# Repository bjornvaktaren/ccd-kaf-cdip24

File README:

To-do
-----

- Check that you can control the servo with 3.3V.
- Change to HX1K with VQ-100 package? Does the logic fit?

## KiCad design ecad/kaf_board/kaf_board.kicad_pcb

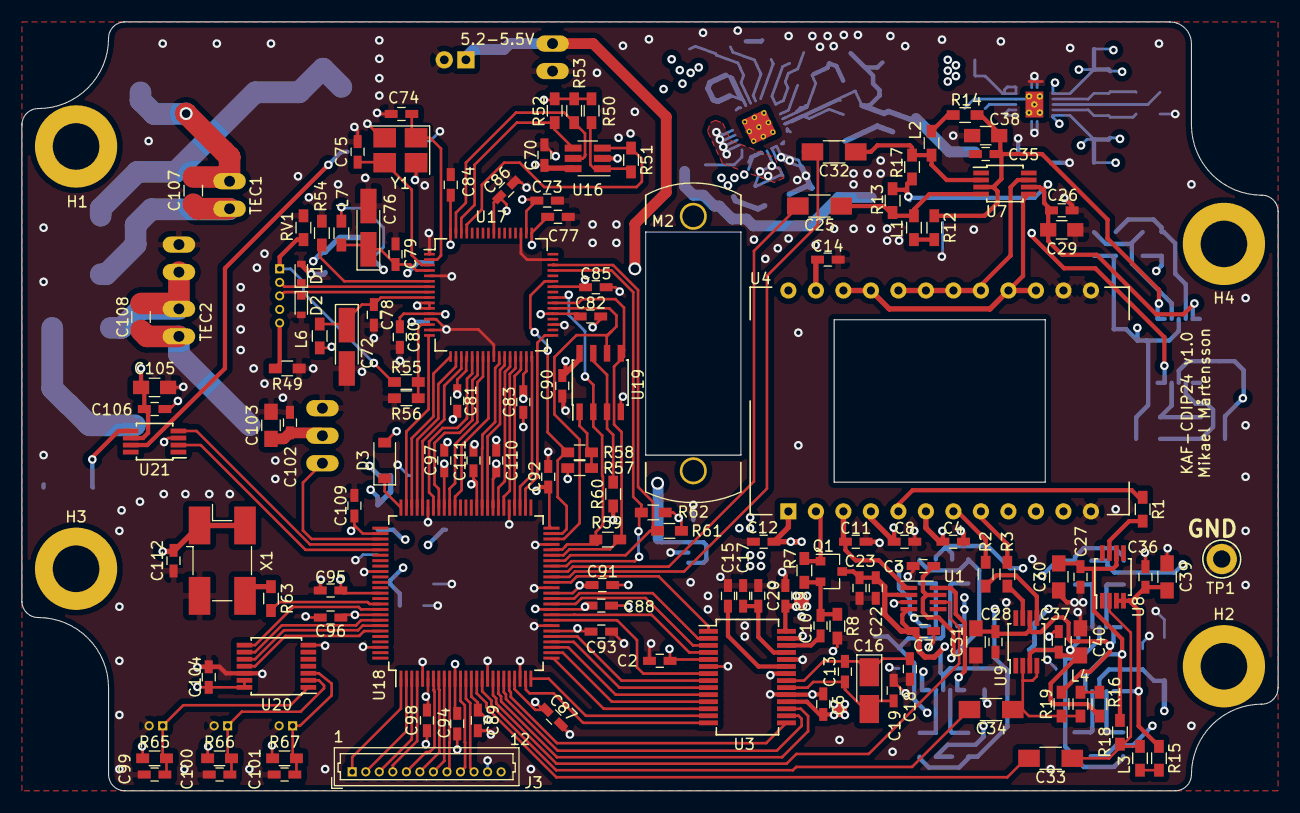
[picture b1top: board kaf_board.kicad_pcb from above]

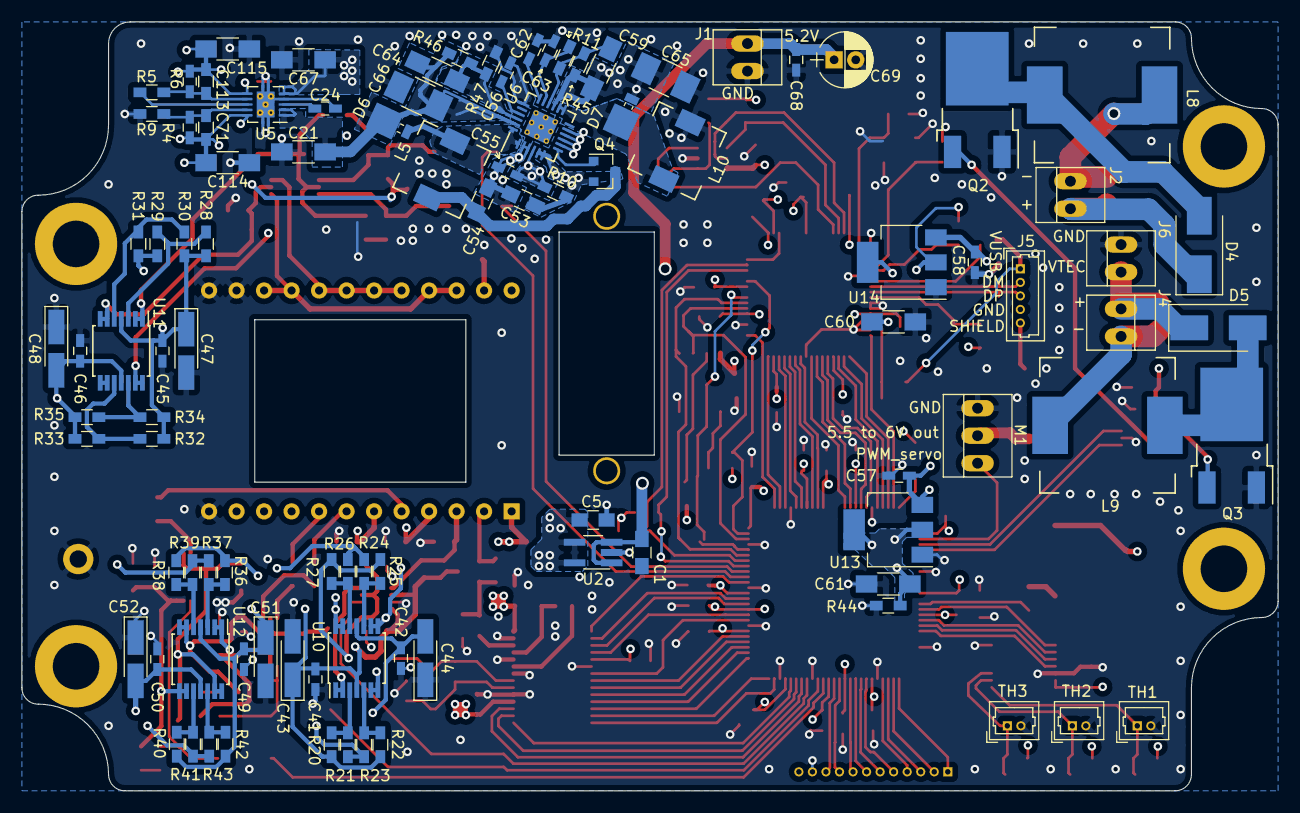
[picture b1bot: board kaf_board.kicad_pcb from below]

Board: 4 copper layers, 116.0 x 71.0 mm, 240 parts (99 on the bottom side), 159 nets.

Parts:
C1, C5: 2.2u X7R; C_0805_HandSoldering
C2, C3, C6, C7, C9, C10, C13, C15, C17, C18, C19, C23, C24, C26, C27, C28, C35, C36, C37, C41, C42, C45, C46, C49, C50, C55, C57, C58, C68, C70, C73, C78, C79, C80, C81, C82, C83, C84, C85, C86, C87, C88, C89, C90, C91, C92, C93, C94, C95, C96, C97, C98, C99, C100, C101, C102, C106, C109, C110, C111, C112: 0.1u; C_0603_HandSoldering
C4, C8, C11, C12, C14: 0; C_0603_HandSoldering
C16: 10u; CP_Tantalum_Case-R_EIA-2012-12_Hand
C20, C22, C104: 1u; C_0603_HandSoldering
C21, C60, C61, C67, C114, C115: 10u; C_1206_HandSoldering
C25, C32, C33, C34: 33u; C_1206_HandSoldering
C29, C30, C31, C38, C39, C40, C53, C54, C103, C105, C107, C108: 4.7u; C_0805_HandSoldering
C43, C44, C47, C48, C51, C52: 4.7u; CP_Tantalum_Case-A_EIA-3216-18_Hand
C56, C71, C113: 10n; C_0603_HandSoldering
C59: populate? No. (5.6p); C_1206_HandSoldering
C62: 4.7n; C_0603_HandSoldering
C63: 220n; C_0603_HandSoldering
C64: 6.8p; C_1206_HandSoldering
C65, C66: 22u; C_1210_HandSoldering
C69: 47u; CP_Radial_D5.0mm_P2.00mm
C72, C76: 4.7u tan; CP_Tantalum_Case-A_EIA-3216-18_Hand
C74, C75: 27p; C_0603_HandSoldering
C77: 3.3u; C_0603_HandSoldering
D1, D2: PGB101; D_0603
D3: 1N5819; D_SOD-123
D4, D5: VS-4EGU06-M3; D_SMB_Handsoldering
D6, D7: MBRM120; D_Powermite_AK
H1, H2, H3, H4: MountingHole; MountingHole_4.3mm_M4_ISO7380_Pad
J1: PWR; PINHEAD1-2
J2: TEC1; PINHEAD1-2
J3: Conn_01x12; Molex_PicoBlade_53047-1210_12x1.25mm_Straight
J4: TEC2; PINHEAD1-2
J5: USB; Molex_PicoBlade_53047-0510_05x1.25mm_Straight
J6: TECPWR; PINHEAD1-2
L1, L2, L3, L4: 1u; L_0603_HandSoldering
L5, L10: 4.7u; L_SMT_B82462G4
L6, L7: 600R/0.5A; L_0603_HandSoldering
L8, L9: 100u; L_Bourns_1210
M1: Motor_Servo; PINHEAD1-3
M2: Servo cut-out; HD-1440A
Q1: MMBT3904LT1G; SOT-23
Q2, Q3: NTD4804N; ONSemi_DPAK-3_5.97x6.35mm
Q4: Si2323DS; SOT-23
R1, R2, R3: 68; R_0603_HandSoldering
R4: 169k 0.1%; R_0603_HandSoldering
R5: 12k 0.1%; R_0603_HandSoldering
R6: 147k 0.1%; R_0603_HandSoldering
R7: 140; R_0603_HandSoldering
R8, R12, R14, R15, R16: 1k; R_0603_HandSoldering
R9: 15k 0.1%; R_0603_HandSoldering
R10: 100; R_0603_HandSoldering
R11: 104.8k; R_0603_HandSoldering
R13, R17, R18, R19, R49: NA; R_0603_HandSoldering
R20, R21, R22, R23, R24, R25, R26, R27, R28, R29, R30, R31, R32, R33, R34, R35, R36, R37, R38, R39, R40, R41, R42, R43: R; R_0603_HandSoldering
R44: 120; R_0603_HandSoldering
R45: 1.3M; R_0603_HandSoldering
R46: 975k; R_0603_HandSoldering
R47: 85.8k; R_0603_HandSoldering
R50, R52, R53, R56, R57, R60, R61, R65, R66, R67: 10k; R_0603_HandSoldering
R51: 2k; R_0603_HandSoldering
R54: 12k 1%; R_0603_HandSoldering
R55: 4.7k; R_0603_HandSoldering
R58, R63: 22; R_0603_HandSoldering
R59: NA(22); R_0603_HandSoldering
R62: 2.2k; R_0603_HandSoldering
RV1: V5.5MLA; R_0603_HandSoldering
TH1, TH2, TH3: 2000, beta 3500; Molex_PicoBlade_53047-0210_02x1.25mm_Straight
TP1: GND; Test_Point_Keystone_5005-5009_Compact
U1: MAX4649; SOT-23-8_Handsoldering
U2: ADP7118AUJZ; TSOT-23-5_HandSoldering
U3: AD9826; SSOP-28_5.3x10.2mm_Pitch0.65mm
U4: KAF-CDIP24; CDIP-24_20.2x34.5mm_P2.54mm
U5: TPS7A39; TI_WSON-10-1TP_3x3mm_P0.5mm_HandSolder
U6: TPS6513x; TI_WQFN-24-1EP_4x4mm_P0.5mm_HandSolder
U7, U8, U21: TC4427; MSOP-8_3x3mm_Pitch0.65mm
U9: TC4428; MSOP-8_3x3mm_Pitch0.65mm
U10, U11, U12: LM224; TSSOP-14_4.4x5mm_Pitch0.65mm
U13: LD1117S12CTR_SOT223; SOT-223-3_TabPin2
U14: LD1117S33CTR_SOT223; SOT-223-3_TabPin2
U16: 93LCxxBxxOT; SOT-23-6_Handsoldering
U17: FT2232HL; LQFP-64_10x10mm_Pitch0.5mm
U18: ICE40HX1K-VQ100; LQFP-100_14x14mm_Pitch0.5mm
U19: W25X20CL; SOIC-8_3.9x4.9mm_Pitch1.27mm
U20: MCP3004; TSSOP-14_4.4x5mm_Pitch0.65mm
X1: KC7050A-C3; Oscillator_SMD_EuroQuartz_XO91-4pin_7.0x5.0mm_HandSoldering
Y1: 12 MHz; Crystal_SMD_3225-4pin_3.2x2.5mm_HandSoldering

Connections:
+1V2: C61.1, C88.1, C94.1, C109.1, C111.1, R44.2, U13.2, U18.11, U18.35, U18.61, U18.77
+3V3: C2.2, C60.1, C70.1, C73.1, C81.1, C83.1, C85.1, C86.1, C87.1, C89.1, C90.1, C91.1, C92.1, C93.1, C95.1, C96.1, C97.1, C98.1, C104.1, C110.1, C112.1, D3.2, J3.12, L6.2, L7.2, R50.1, R52.1, R53.1, R57.2, R60.1, R61.1, R62.1, R65.1, R66.1, R67.1, U3.5, U14.2, U16.6, U17.20, U17.31, U17.42, U17.50, U17.56, U18.6, U18.14, U18.22, U18.31, U18.38, U18.50, U18.58, U18.67, U18.88, U18.92, U19.8, U20.13, U20.14, X1.1, X1.4
+6V: C1.2, C53.1, C57.1, C58.1, C68.1, C69.1, C102.1, C103.1, J1.1, M1.2, Q4.2, R10.2, U2.1, U2.3, U6.5, U6.6, U13.3, U14.3
+14.5V: C7.2, C22.2, C23.2, C41.2, C43.1, C45.2, C47.1, C49.2, C51.1, C71.2, C114.2, Q1.3, R4.1, R20.1, R22.1, R24.1, R26.1, R28.1, R30.1, R32.1, R34.1, R36.1, R38.1, R40.1, R42.1, U1.2, U1.4, U5.10, U10.4, U11.4, U12.4
-14.5V: C3.2, C42.2, C44.2, C46.2, C48.2, C50.2, C52.2, C113.1, C115.2, R6.2, R21.2, R23.2, R25.2, R27.2, R29.2, R31.2, R33.2, R35.2, R37.2, R39.2, R41.2, R43.2, U1.7, U5.6, U10.11, U11.11, U12.11
/ccd/AD_ADCLK: U3.3, U18.36
/ccd/AD_CDSCLK1: U3.1, U18.40
/ccd/AD_CDSCLK2: U3.2, U18.37
/ccd/AD_D0: U3.14, U18.24
/ccd/AD_D1: U3.13, U18.25
/ccd/AD_D2: U3.12, U18.26
/ccd/AD_D3: U3.11, U18.27
/ccd/AD_D4: U3.10, U18.28
/ccd/AD_D5: U3.9, U18.29
/ccd/AD_D6: U3.8, U18.30
/ccd/AD_D7: U3.7, U18.33
/ccd/AD_OEB: U3.4, U18.34
/ccd/AD_SCLK: U3.16, U18.20
/ccd/AD_SDATA: U3.15, U18.21
/ccd/AD_SLOAD: U3.17, U18.19
/ccd/AMP_OFF: U1.6, U18.18
/ccd/AVDD: C5.2, C6.2, C9.2, U2.4, U2.5, U3.18, U3.28
/ccd/H1: R2.2, U9.5
/ccd/H2: R3.2, U9.7
/ccd/H_3.3V: C34.2, U18.16
/ccd/R: R1.2, U8.7
/ccd/R_3.3V: C33.2, U18.15
/ccd/V1: U4.15, U4.16, U4.21, U4.22, U7.5
/ccd/V1_3.3V: C25.2, U18.42
/ccd/V2: U4.17, U4.18, U4.19, U4.20, U7.7
/ccd/VGUARD: C14.1, U4.23, U11.13, U11.14
/ccd/VOG: C12.1, U4.1, U10.6, U10.7
/ccd/VOUT_BUF: C10.1, Q1.2, R7.1, R8.1
/ccd/VRD: C8.1, U4.4, U10.8, U10.9
/ccd/VSS: C4.1, U4.6, U10.13, U10.14
/ccd/V_AMP: C11.1, U1.1, U4.3
/ccd/V_AMPL: U1.8, U10.1, U10.2
/ccd/V_HH: C28.2, C31.2, R19.1, U9.6, U12.6, U12.7
/ccd/V_HL: C37.2, C40.2, R16.1, U9.3, U12.1, U12.2
/ccd/V_RH: C27.2, C30.2, R18.1, U8.6, U12.13, U12.14
/ccd/V_RL: C36.2, C39.2, R15.1, U8.3, U8.4, U12.8, U12.9
/ccd/V_VH: C26.2, C29.2, R13.1, R17.1, U7.6, U11.6, U11.7
/ccd/V_VL: C35.2, C38.2, R12.1, R14.1, U7.3, U11.1, U11.2
/ccd/ccd_voltage_2/V3: U11.8, U11.9
/fpga/AUX1: J3.1, U18.1
/fpga/AUX2: J3.2, U18.2
/fpga/AUX3: J3.3, U18.3
/fpga/AUX4: J3.4, U18.4
/fpga/AUX5: J3.5, U18.7
/fpga/AUX6: J3.6, U18.8
/fpga/AUX7: J3.7, U18.9
/fpga/AUX8: J3.8, U18.10
/fpga/AUX9: J3.9, U18.12
/fpga/AUX10: J3.10, U18.13
/fpga/CLK: R63.1, U18.90
/fpga/FT_CLKOUT: U17.32, U18.53
/fpga/FT_D0: U17.16, U18.74
/fpga/FT_D1: U17.17, U18.73
/fpga/FT_D2: U17.18, U18.72
/fpga/FT_D3: U17.19, U18.71
/fpga/FT_D4: U17.21, U18.69
/fpga/FT_D5: U17.22, U18.68
/fpga/FT_D6: U17.23, U18.66
/fpga/FT_D7: U17.24, U18.65
/fpga/FT_OE#: U17.33, U18.52
/fpga/FT_RD#: U17.28, U18.57
/fpga/FT_RXF#: U17.26, U18.60
/fpga/FT_SIWUA: U17.30, U18.54
/fpga/FT_TXE#: U17.27, U18.59
/fpga/FT_WR#: U17.29, U18.56
/fpga/MCP_CLK: U18.95, U20.11
/fpga/MCP_CS_N: U18.91, U20.8
/fpga/MCP_DIN: U18.93, U20.9
/fpga/MCP_DOUT: U18.94, U20.10
/fpga/PWM_SERVO: M1.1, U18.78
/fpga/PWM_TEC1: U18.80, U21.2
/fpga/PWM_TEC2: U18.79, U21.4
/fpga/V1_3.3V: C32.2, U18.41
/fpga/VPP_2V5: D3.1, U18.75
/power/+15V: C21.2, C64.1, C66.1, D6.1, R46.2, U5.1, U5.2, U6.23
/power/-15V: C59.2, C65.1, C67.2, D7.2, R45.1, U5.5, U6.15
/thermo_and_mechanical/V_TEC: C105.1, C106.1, C107.1, C108.1, D4.1, D5.1, J2.1, J4.1, J6.1, U21.6
/usb-interface/DM: D1.1, J5.2, U17.7
/usb-interface/DP: D2.1, J5.3, U17.8
/usb-interface/FT_CDONE: R62.2, U17.45, U18.43
/usb-interface/FT_CRESET: R61.2, U17.46, U18.44
/usb-interface/FT_MISO: R59.1, U17.40, U18.46, U19.2
/usb-interface/FT_MOSI: R59.2, U17.39, U18.45, U19.5
/usb-interface/FT_SCK: U17.38, U18.48, U19.6
/usb-interface/FT_SS: R58.1, U17.43, U18.49
/usb-interface/VPHY: C76.1, C79.1, L7.1, U17.4
/usb-interface/VREG: C77.1, C80.1, C82.1, C84.1, U17.12, U17.37, U17.49, U17.64
/usb-interface/VUSB: J5.1, R55.2, RV1.2
GND: C1.1, C2.1, C3.1, C4.2, C5.1, C6.1, C7.1, C8.2, C9.1, C11.2, C12.2, C14.2, C15.2, C17.1, C18.2, C19.2, C20.1, C21.1, C22.1, C23.1, C24.1, C26.1, C27.1, C28.1, C29.1, C30.1, C31.1, C35.1, C36.1, C37.1, C38.1, C39.1, C40.1, C41.1, C42.1, C43.2, C44.1, C45.1, C46.1, C47.2, C48.1, C49.1, C50.1, C51.2, C52.1, C53.2, C54.2, C55.2, C56.2, C57.2, C58.2, C60.2, C61.2, C62.2, C63.2, C65.2, C66.2, C67.1, C68.2, C69.2, C70.2, C72.2, C73.2, C74.2, C75.1, C76.2, C77.2, C78.2, C79.2, C80.2, C81.2, C82.2, C83.2, C84.2, C85.2, C86.2, C87.2, C88.2, C89.2, C90.2, C91.2, C92.2, C93.2, C94.2, C95.2, C96.2, C97.2, C98.2, C99.2, C100.2, C101.2, C102.2, C103.2, C104.2, C105.2, C106.2, C109.2, C110.2, C111.2, C112.2, C114.1, C115.1, D1.2, D2.2, J1.2, J3.11, J5.4, J6.2, L10.1, M1.3, Q2.3, Q3.3, R8.2, R9.2, R44.1, R47.1, R49.1, R54.1, R56.2, RV1.1, TH1.2, TH2.2, TH3.2, TP1.1, U1.3, U2.2, U3.6, U3.19, U3.22, U3.24, U3.27, U4.12, U4.13, U4.14, U5.4, U5.11, U6.2, U6.3, U6.19, U6.25, U13.1, U14.1, U16.2, U17.1, U17.5, U17.10, U17.11, U17.13, U17.15, U17.25, U17.35, U17.47, U17.51, U18.5, U18.17, U18.23, U18.32, U18.39, U18.47, U18.55, U18.70, U18.84, U18.98, U19.4, U20.7, U20.12, U21.3, X1.2, Y1.2, Y1.4
GNDPWR: J5.5, R49.2
unnamed: C10.2, U3.26
unnamed: C13.1, C16.2, C19.1, U3.20
unnamed: C13.2, C16.1, C18.1, U3.21
unnamed: C15.1, U3.23
unnamed: C17.2, C20.2, U3.25
unnamed: C24.2, U5.3
unnamed: C25.1, L1.2, R13.2, U7.4
unnamed: C32.1, L2.2, R17.2, U7.2
unnamed: C33.1, L3.2, R18.2, U8.2
unnamed: C34.1, L4.2, R19.2, U9.2, U9.4
unnamed: C54.1, L5.2, Q4.3
unnamed: C55.1, R10.1, U6.4, U6.8, U6.9, U6.10, U6.11
unnamed: C56.1, U6.21
unnamed: C59.1, R11.1, R45.2, U6.16
unnamed: C62.1, U6.18
unnamed: C63.1, R11.2, U6.17
unnamed: C64.2, R46.1, R47.2, U6.22
unnamed: C71.1, R4.2, R9.1, U5.9
unnamed: C72.1, C78.1, L6.1, U17.9
unnamed: C74.1, U17.2, Y1.1
unnamed: C75.2, U17.3, Y1.3
unnamed: C99.1, R65.2, TH1.1, U20.1
unnamed: C100.1, R66.2, TH2.1, U20.2
unnamed: C101.1, R67.2, TH3.1, U20.3
unnamed: C107.2, J2.2, L8.1
unnamed: C108.2, J4.2, L9.1
unnamed: C113.2, R5.2, R6.1, U5.7
unnamed: D4.2, L8.2, Q2.2, Q2.4
unnamed: D5.2, L9.2, Q3.2, Q3.4
unnamed: D6.2, L5.1, U6.1, U6.24
unnamed: D7.1, L10.2, U6.13, U6.14
unnamed: L1.1, R12.2
unnamed: L2.1, R14.2
unnamed: L3.1, R15.2
unnamed: L4.1, R16.2
unnamed: Q1.1, R7.2, U4.2
unnamed: Q2.1, U21.7
unnamed: Q3.1, U21.5
unnamed: Q4.1, U6.7
unnamed: R1.1, U4.5
unnamed: R2.1, U4.7
unnamed: R3.1, U4.8
unnamed: R5.1, U5.8
unnamed: R20.2, R21.1, U10.3
unnamed: R22.2, R23.1, U10.5
unnamed: R24.2, R25.1, U10.10
unnamed: R26.2, R27.1, U10.12
unnamed: R28.2, R29.1, U11.3
unnamed: R30.2, R31.1, U11.5
unnamed: R32.2, R33.1, U11.10
unnamed: R34.2, R35.1, U11.12
unnamed: R36.2, R37.1, U12.3
unnamed: R38.2, R39.1, U12.5
unnamed: R40.2, R41.1, U12.10
unnamed: R42.2, R43.1, U12.12
unnamed: R50.2, R51.2, U16.1
unnamed: R51.1, U16.3, U17.61
unnamed: R52.2, U16.4, U17.62
unnamed: R53.2, U16.5, U17.63
unnamed: R54.2, U17.6
unnamed: R55.1, R56.1, U17.14
unnamed: R57.1, R58.2, U19.1
unnamed: R60.2, U19.3, U19.7
unnamed: R63.2, X1.3

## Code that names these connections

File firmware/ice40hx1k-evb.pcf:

set_io clk_in          90
set_io mcp_dclk        95
set_io mcp_dout        94
set_io mcp_din         93
set_io mcp_cs_n        91
set_io ft_bus[0]       74
set_io ft_bus[1]       73
set_io ft_bus[2]       72
set_io ft_bus[3]       71
set_io ft_bus[4]       69
set_io ft_bus[5]       68
set_io ft_bus[6]       66
set_io ft_bus[7]       65
set_io ft_rxf_n        60
set_io ft_txe_n        59
set_io ft_rd_n         57
set_io ft_wr_n         56
set_io ft_siwu_n       54
set_io ft_clkout       53
set_io ft_oe_n         52
set_io pwm_shutter     78
set_io pwm_peltier_1   80
set_io pwm_peltier_2   79
set_io ad_adclk        36
set_io ad_cdsclk1      40
set_io ad_cdsclk2      37
set_io ad_oeb_n        34
set_io kaf_amp         18
set_io kaf_h1          16
set_io kaf_r           15
set_io kaf_v1          41
set_io kaf_v2          42
set_io ad_data[0]      24
set_io ad_data[1]      25
set_io ad_data[2]      26
set_io ad_data[3]      27
set_io ad_data[4]      28
set_io ad_data[5]      29
set_io ad_data[6]      30
set_io ad_data[7]      33
set_io ad_sload        19
set_io ad_sclk         20
set_io ad_sdata        21
#set_io debug[0]        1
#set_io debug[1]        3
#set_io debug[2]        7
#set_io debug[3]        9
#set_io debug[4]        12

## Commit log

2020-03-17 added simulation of bias tee and stuff
2020-03-22 added custum libraries and latest changes
2020-03-22 started adding thermistors and peltier control
2020-03-26 Added PWM signals
2020-03-26 minor changes
2020-04-09 added two power supplies
2020-04-09 added a power supply
2020-04-12 updates to schematics
2020-04-12 starting on the software: currently getting and plotting temperature
2020-04-12 started adding fpga firmware
2020-04-13 started to add tx fifo in the firmware
2020-04-17 added separate read clock to fifomem to get yosys to infer BRAM
2020-04-17 small step towards gettin fifo to work, but waddr is never incremented
2020-04-19 ft245 interface to fpga semms to be working with the newly added fifos
2020-04-24 FT245 interface seems to be working, but missing 2 bits from the MCP
2020-04-25 Fixed the MCP error
2020-04-27 The MCP now reads two thermistor values
2020-05-02 updated schematics. Mainly supplies
2020-05-03 Sampling two NTCs finally work very well
2020-05-03 switched to single-ended temperature measurement
2020-05-03 Servo controller for the camera shutter implemented in FPGA
2020-05-05 Fixed servo pwm delay between pulses
2020-05-06 Can now set PWM value, but somehow it broke the temperature query...
2020-05-08 Setting the PWM value works, but the subsequent temperature query return jibberish 1/10 of the time after. If the PWM is not set, everything else works as expected.
2020-05-08 added extra states when writing data to tx fifo - seems to work
2020-05-12 started associating footprints
2020-05-17 associating footprints
2020-05-17 started adding ccd readout to firmware
2020-05-22 finished assigning footprints
2020-05-26 continued placing footprints
2020-05-29 added board outline
2020-05-31 continued footprint placement
2020-05-31 started implementing the AD9826 configuration module
2020-05-31 started adding the ad9826 config module to top/-level and testbench
2020-06-04 firmware: continued working on ad config module and integration into top-level
2020-06-05 ad9826 config module writing works in simulation
2020-06-05 changes schematics and PCB to ice40hx1k-vq100
2020-06-07 added oscillator to fpga. footprint placement
2020-06-09 changed all board i/o to go through a pin header and placed power components
2020-06-11 have made a preliminary placement of components
2020-06-12 changed some connectors and moved components
2020-06-14 Started routing PCB
2020-06-14 continued routing
2020-06-26 Changed +-15 DC/DC converter and routed it.
2020-06-28 Power plane design and started routing the CCD circuit supplies
2020-06-28 Most things connected on PCB except GND. Doing ERC.
2020-07-01 PCB design finished. Will go over the traces once more.
2020-07-01 Minor changes to PCB
2020-07-03 Decided to ditch the TL432 in favour of a +-14.5V LDO regulator. Need to re-route a lot of stuff
2020-07-05 Replaced the MAX743 +-15V converted with another. Not yet routed.
2020-07-05 Routed the +-15V converter
2020-07-05 Placed +-15V converter
2020-07-16 Last changes before sending PCB to manufacturing
2020-08-28 Started testing the PCBA. Changed FTDI connection string from UM232H to FT2232H. Added EEPROM config file for FT2232H.
2020-08-29 Mostly readme updates
2020-09-04 Marked R59 as NA, i.e. it should not be populated.
2020-09-04 Trying to get FT245 interface to work with the FPGA.
2020-09-04 renamed top level vhdl module
2020-09-05 The FT245 interface of the FPGA works, but if I enable the ccd_toggle state it gets stuck waiting for the ccd even though the ccd toggle command is not sent.
2020-09-05 Reading two temperature sensors works
2020-09-06 Added a tx_mux module to the firmware
2020-09-06 Started changing MCP interface to a state machine
2020-09-08 Finished rewriting mcp interface
2020-09-08 Started on a test bench for ad9826_config. It does not work yet
2020-09-11 Corrected some bugs in ad9826_config module
2020-09-11 makefile update for firmware
2020-09-11 Completely rewrote ad9826_config
2020-09-11 started to update top-level firmware with the re-written firmware modules
2020-09-11 Added SR latch module and started updating top testbench.
2020-09-11 Ranomize the seed when routing
2020-09-12 Finished integrating MCP interface with top
2020-09-16 Reading and writing to ad9826 config register works in simulation
2020-09-16 reading ad9826 configuration register now ACTUALLY works in simulation
2020-09-16 Setting FPGA registers works in simulation
2020-09-16 Working toward gettinf ccd_readout firmware to work in sumulation
2020-09-17 working towards getting the ccd_readout module to work in simulation
2020-09-18 ccd_readout module works in simulation. Something wrong with reading from FPGA. Software or firmware issue?
2020-09-24 started rewriting the ft245 interface as a FSM
2020-09-25 new ft245 interface might work in silulation :)
2020-09-27 software debugging
2020-09-27 minor firmware update
2020-09-27 Trying to get writing from FPGA to work
2020-09-30 Finally got some data out of the FPGA! It is sometimes late by 1 clock
2020-10-01 Sending data from FPGA works and looks stable!
2020-10-01 Started add ing decoding of FPGA data packets in software
2020-10-02 Starting to change ad9826_conf to remove sr_latch
2020-10-04 Untested software update: decode temperature reading.
2020-10-04 Makefile updates and started adding indigo driver
2020-10-08 Continued with indigo driver
2020-10-08 Fixed conversion of ADC values to temperature in software.
2020-10-09 Got reading AD9826 configuration register to work in firmware
2020-10-09 Added debug option and started to add reading of AD9826 config in software.
2020-10-11 Setting and getting AD9826 settings, except offset, is possible
2020-10-12 Continued implementing indigo driver
2020-10-16 Corrected two resistors I had flipped on silk screen. Corrected to cap values
2020-10-16 Created a PID regulator in software
2020-10-16 Some improvements to PID class
2020-10-18 Added PID regulator to Camera class.
2020-10-18 Removed SR latch from CCD readout module
2020-10-18 Added extra state to toggle CCD readout in firmware
2020-10-22 Updates to schematics after testing the PCA
2020-10-22 removed a critical path for clk in firmware
2020-10-25 Added software to read out image from sensor
2020-10-25 Removed capacitor that made the DC/DC booster/inverter output -21V
2020-10-25 updated number of pixels in firmware to match datasheet of KAF-3200
2020-10-25 Added some temporary debug messages
2020-10-29 Fixes to software and firmware
2020-11-07 Reading out seems to work but fpga is not waiting if FTDI is full
2020-11-08 Think I got CCD readout to work! Will attach CCD chip
2020-11-18 Reading out CCD works
2020-11-18 Added CAD drawing of optical window
2020-12-25 Fixed flipped gate and source on mosfets
2020-12-25 Software and firmware updates
2021-01-12 Readout is still missing a few pixels in each frame
2021-01-17 Fixed sensor readout
2021-01-31 Changed tx_fifo depth. Calibrated shutter.
2021-02-03 Added option to take dark frame
2021-02-06 Timing diagram for ccd readout
2021-02-06 Updated ccd_readout module and corresponding in software
2021-02-07 Added terminal mode to main. Faster readout of CCD
2021-02-08 added batch exposures
2021-02-09 Fixed small stupid error
2021-02-10 Corrected PID class and added more functionallity to main
2021-02-13 Added small overlap between V clocks
2021-02-13 Set default gain. Trying to debug why offset is not set
2021-02-21 Better FT245 module
2021-02-21 Trimmed PID and formatted some debug messages
2021-02-22 CCD readout seems to work on both USB 3 and old slow computer with USB 2
2022-03-03 Delayed read pointer for FIFO 1 clock. Now it works very well!
2022-03-14 Started to add formal verification (symbiyosys) of fifo
2022-09-12 Started adding formal verification for ft245 module
2022-09-18 Added testbench for ft245 and fifo loopback. Changed prioroty if read and write on ft245 interface.
2022-09-18 Speed up ft245 write
2024-02-06 Ft245 interface
2024-03-01 Started rewriting for testability. Broke out camera configuration in its own class
2024-12-15 More unit tests for CameraConfiguration
